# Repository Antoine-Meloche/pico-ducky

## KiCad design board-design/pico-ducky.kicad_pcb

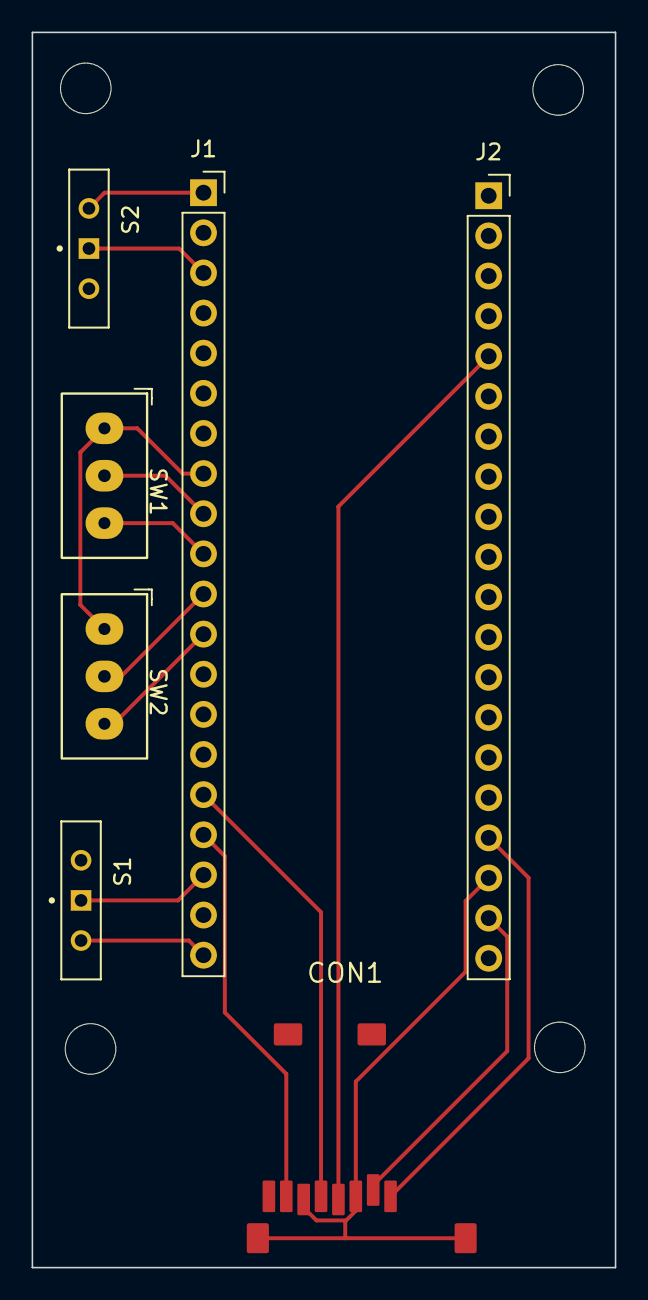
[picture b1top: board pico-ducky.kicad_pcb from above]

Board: 2 copper layers, 36.9 x 78.2 mm, 7 parts (0 on the bottom side), 13 nets.

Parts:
CON1: CardSlot_MicroSD_YamaichiPJS008U-3000
J1, J2: Conn_01x20_Female; PinSocket_1x20_P2.54mm_Vertical
S1, S2: MSS-102545-14A-D; SW_MSS-102545-14A-D
SW1, SW2: Slide_Switch_SPDT_P3mm_10x5x10mm

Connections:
unnamed: CON1.2 (CD/DAT3), J2.19
unnamed: CON1.3 (CMD), CON1.6 (VSS), CON1.9 (SHELL1), CON1.10 (SHELL2), J2.18
unnamed: CON1.1 (DAT2), J2.17
unnamed: CON1.4 (VDD), J2.5
unnamed: J1.1, S2.2
unnamed: J1.3, S2.1
unnamed: J1.8, SW1.1, SW2.1
unnamed: J1.9, SW1.2
unnamed: J1.10, SW1.3
unnamed: J1.11, SW2.2
unnamed: J1.12, SW2.3
unnamed: J1.18, S1.1
unnamed: J1.20, S1.3

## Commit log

2023-04-26 Added microSD reader and changed switches
2023-05-09 FEAT: Added functions, while loops and formatted code
2023-05-10 Added STRINGLN, removed unecessary IF code
2023-05-11 Added caps lock check for OS detection
2023-05-12 Added REM_BLOCK, WIFI, CONNECT_WIFI, ATTACKMODE
    Attackmode is still missing support for VID, PID, MAn, PROD and SERIAL (which will hopefully be implemented in the future)
